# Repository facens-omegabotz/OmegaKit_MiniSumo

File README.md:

# OmegaKit MiniSumo

Repositório dedicado aos projetos de placas de circuito impresso (PCI) desenvolvidas para a categoria Mini Sumô - 500g (Autônomo | RC).

## OmegaKit FX50

Esta pasta diz respeito à versão da placa desenhada para os sensores FX50, da Fox Dynamics. A principal diferença deste desenho para o OmegaKit_RZ60 é a presença de LEDs para a sinalização de recepção de sinal.

[Datasheet FX50](https://github.com/luisf18/FXDevices/blob/main/Sensor_FXS50/Datasheet_FX_S50.pdf)

[Projeto esquemático OmegaKit FX50](./OmegaKit_FX50/OmegaKit_FX50.pdf)

## OmegaKit RZ60

Esta pasta diz respeito à versão da placa desenhada para os sensores RZ60s, da Sumozade. Esta placa liga diretamente os sensores à placa, visto que há LEDs na parte de trás dos sensores para sinalização de detecção.

[Informações RZ60s](https://sumozade.com/rz60s-digital-infrared-sensor--0-60-cm-)

[Projeto esquemático OmegaKit RZ60](./OmegaKit_RZ60/OmegaKit_RZ60.pdf)

## Omegakit Junior

Esta pasta diz respeito à versão da placa dedicada à nova categoria de mini sumô autônomo para juniores. Ela utiliza um Arduino Nano ao invés de um ESP32 DEVKIT V1, e possui 5 entradas analógicas para uso, visto que o Arduino Nano pode converter entradas analógicas em digitais de acordo com a necessidade.

[Projeto esquemático OmegaKit Junior](./OmegaKit_Junior/OmegaKit_Junior.pdf)

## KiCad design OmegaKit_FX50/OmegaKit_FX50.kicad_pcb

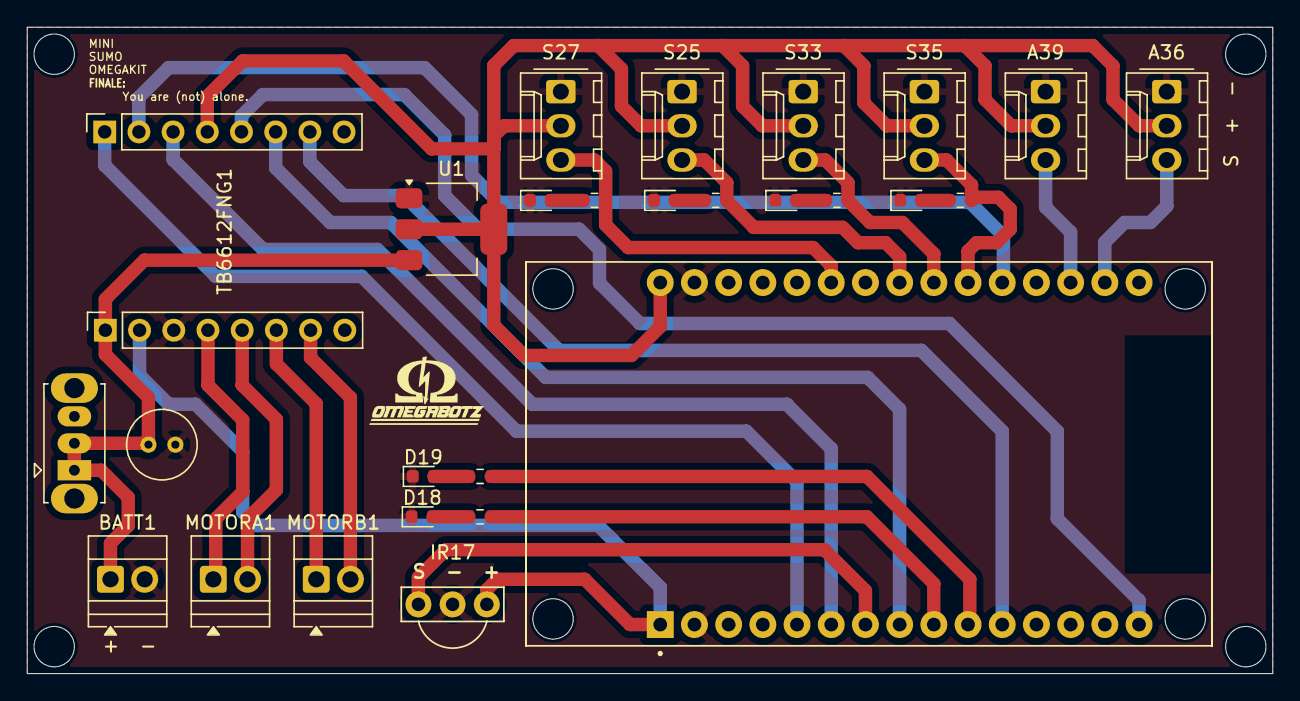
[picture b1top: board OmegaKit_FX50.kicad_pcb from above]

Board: 2 copper layers, 92.5 x 48.0 mm, 27 parts (0 on the bottom side), 29 nets.

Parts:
A36, A39: Conn_01x03_Pin; Molex_KK-254_AE-6410-03A_1x03_P2.54mm_Vertical
BATT1: Borne; TerminalBlock_Xinya_XY308-2.54-2P_1x02_P2.54mm_Horizontal
C1: C_US; C_Radial_D5.0mm_H5.0mm_P2.00mm
D18, D19: LED; LED_0603_1608Metric
DS1, DS2, DS3, DS4: LED; LED_0603_1608Metric
ESP1: ESP32-DEVKIT-V1; MODULE_ESP32_DEVKIT_V1
IR17: TSOP1838
MOTORA1: Borne; TerminalBlock_Xinya_XY308-2.54-2P_1x02_P2.54mm_Horizontal
MOTORB1: Borne; TerminalBlock_Xinya_XY308-2.54-2P_1x02_P2.54mm_Horizontal
R1, R2: 220R; R_0603_1608Metric
RS1, RS2, RS3, RS4: 220R; R_0603_1608Metric
S25, S27, S33, S35: Conn_01x03_Pin; Molex_KK-254_AE-6410-03A_1x03_P2.54mm_Vertical
SW1: SW_CK_OS102011MS2Q; SW_Slide_SPDT_Straight_CK_OS102011MS2Q
TB6612FNG1: Socket_TB6612FNG
U1: AMS1117-5.0; SOT-223-3_TabPin2

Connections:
/A1: A36.3, ESP1.17 (VP)
/A2: A39.3, ESP1.18 (VN)
/AIN1: ESP1.6 (RX2), TB6612FNG1.14 (AIN1)
/AIN2: ESP1.20 (D35), TB6612FNG1.15 (AIN2)
/A_GND: MOTORA1.2, TB6612FNG1.5 (A02)
/A_VCC: MOTORA1.1, TB6612FNG1.4 (A01)
/BATT_VCC: BATT1.1, C1.1, SW1.1 (B), SW1.2 (C), TB6612FNG1.1 (VM), U1.3 (VI)
/BIN1: ESP1.15 (D23), TB6612FNG1.12 (BIN1)
/BIN2: ESP1.8 (D5), TB6612FNG1.11 (BIN2)
/B_GND: MOTORB1.2, TB6612FNG1.7 (B01)
/B_VCC: MOTORB1.1, TB6612FNG1.6 (B02)
/IR_SIGNAL: ESP1.7 (TX2), IR17.1 (OUT)
/LED1: ESP1.10 (D19), R1.2
/LED2: ESP1.9 (D18), R2.2
/PWMA: ESP1.5 (D4), TB6612FNG1.16 (PWMA)
/PWMB: ESP1.11 (D21), TB6612FNG1.10 (PWMB)
/S1: ESP1.21 (D32), RS1.2, S35.3
/S2: ESP1.22 (D33), RS2.2, S33.3
/S3: ESP1.23 (D25), RS3.2, S25.3
/S4: ESP1.25 (D27), RS4.2, S27.3
/VCC: ESP1.1 (3V3), IR17.3 (VCC), TB6612FNG1.2 (VCC)
/V_REG: A36.2, A39.2, ESP1.30 (VIN), S25.2, S27.2, S33.2, S35.2, TB6612FNG1.13 (STBY), U1.2 (VO)
GND: A36.1, A39.1, BATT1.2, C1.2, D18.1 (K), D19.1 (K), DS1.1 (K), DS2.1 (K), DS3.1 (K), DS4.1 (K), ESP1.2 (GND), ESP1.29 (GND), IR17.2 (GND), S25.1, S27.1, S33.1, S35.1, TB6612FNG1.3 (GND), U1.1 (GND)
unnamed: D18.2 (A), R2.1
unnamed: D19.2 (A), R1.1
unnamed: DS1.2 (A), RS1.1
unnamed: DS2.2 (A), RS2.1
unnamed: DS3.2 (A), RS3.1
unnamed: DS4.2 (A), RS4.1

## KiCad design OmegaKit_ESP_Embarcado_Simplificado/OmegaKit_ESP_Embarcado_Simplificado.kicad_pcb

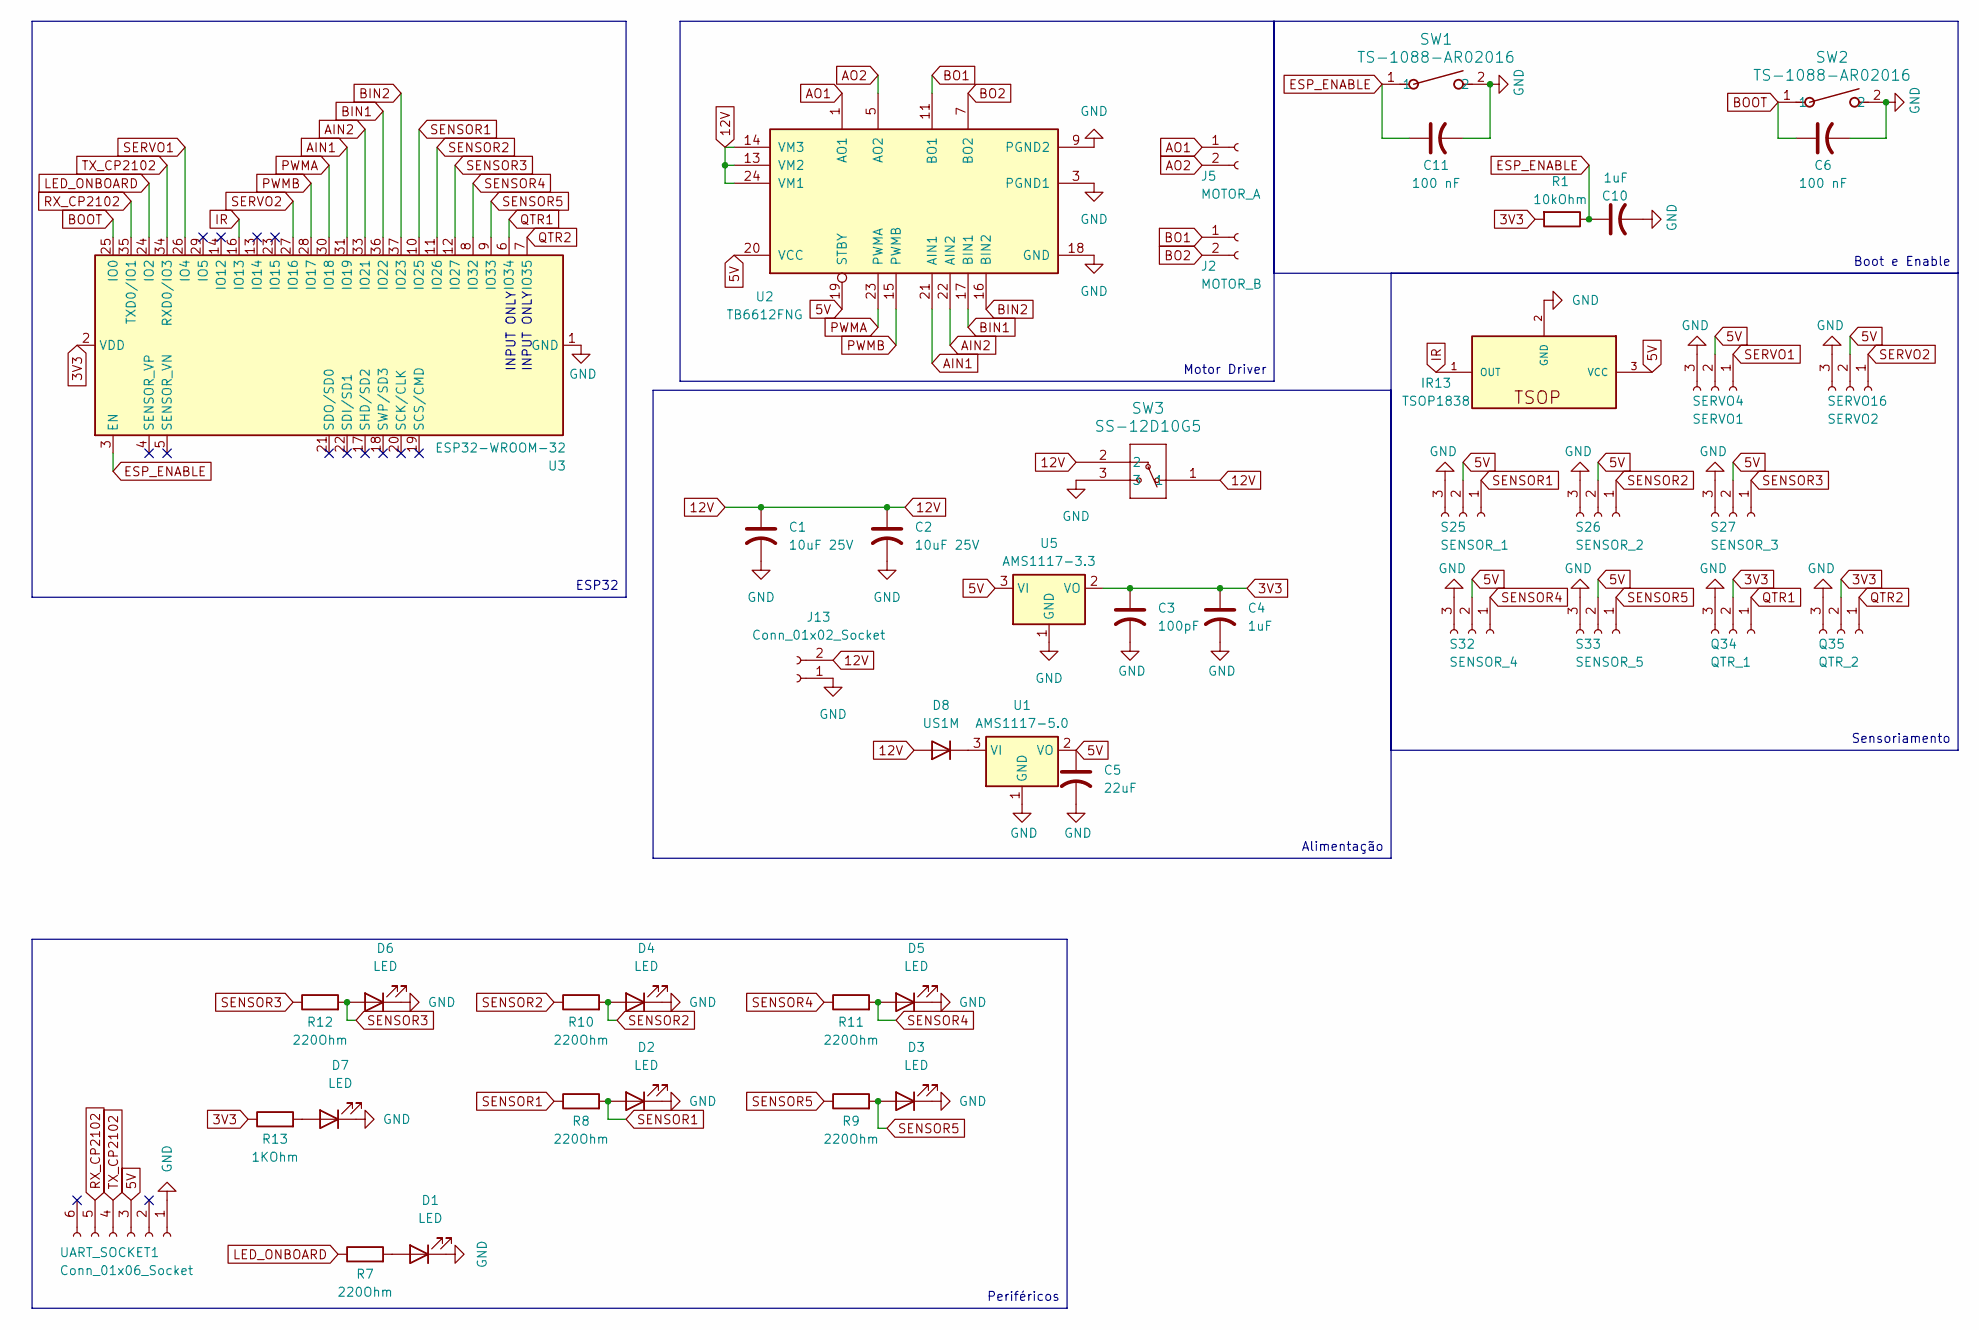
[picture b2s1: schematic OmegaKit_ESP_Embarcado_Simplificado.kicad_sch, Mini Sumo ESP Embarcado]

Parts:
C1, C2: 10uF 25V; C_Elec_4x5.4
C3: 100pF; C_0603_1608Metric_Pad1.08x0.95mm_HandSolder
C4, C10: 1uF; C_0402_1005Metric_Pad0.74x0.62mm_HandSolder
C5: 22uF; C_0603_1608Metric_Pad1.08x0.95mm_HandSolder
C6, C11: 100 nF; C_0201_0603Metric_Pad0.64x0.40mm_HandSolder
D1, D2, D3, D4, D5, D6, D7: LED; LED_0805_2012Metric_Pad1.15x1.40mm_HandSolder
D8: US1M; D_SMA_Handsoldering
IR13: TSOP1838
J2: MOTOR_B; PinHeader_1x02_P2.54mm_Vertical
J5: MOTOR_A; PinHeader_1x02_P2.54mm_Vertical
J13: Conn_01x02_Socket; PinHeader_1x02_P2.54mm_Vertical
Q34: QTR_1; PinHeader_1x03_P2.54mm_Vertical
Q35: QTR_2; PinHeader_1x03_P2.54mm_Vertical
R1: 10kOhm; R_0603_1608Metric_Pad0.98x0.95mm_HandSolder
R7, R8, R9, R10, R11, R12: 220Ohm; R_0805_2012Metric_Pad1.20x1.40mm_HandSolder
R13: 1KOhm; R_0805_2012Metric_Pad1.20x1.40mm_HandSolder
S25: SENSOR_1; PinHeader_1x03_P2.54mm_Vertical
S26: SENSOR_2; PinHeader_1x03_P2.54mm_Vertical
S27: SENSOR_3; PinHeader_1x03_P2.54mm_Vertical
S32: SENSOR_4; PinHeader_1x03_P2.54mm_Vertical
S33: SENSOR_5; PinHeader_1x03_P2.54mm_Vertical
SERVO4: SERVO1; PinHeader_1x03_P2.54mm_Vertical
SERVO16: SERVO2; PinHeader_1x03_P2.54mm_Vertical
SW1, SW2: TS-1088-AR02016; SW_TS-1088_XNP
SW3: SS-12D10G5; SS-12D10G5_XKB
U1: AMS1117-5.0; SOT-223-3_TabPin2
U2: TB6612FNG; SSOP-24_5.3x8.2mm_P0.65mm
U3: ESP32-WROOM-32
U5: AMS1117-3.3; SOT-223-3_TabPin2
UART_SOCKET1: Conn_01x06_Socket; PinHeader_1x06_P2.54mm_Vertical

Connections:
3V3: C3.1, C4.1, Q34.2, Q35.2, R1.2, R13.1, U3.2 (VDD), U5.2 (VO)
5V: C5.1, IR13.3 (VCC), S25.2, S26.2, S27.2, S32.2, S33.2, SERVO4.2, SERVO16.2, U1.2 (VO), U2.19 (STBY), U2.20 (VCC), U5.3 (VI), UART_SOCKET1.3
12V: C1.1, C2.1, D8.2 (A), J13.2, SW3.1, SW3.2, U2.13 (VM2), U2.14 (VM3), U2.24 (VM1)
AIN1: U2.21 (AIN1), U3.31 (IO19)
AIN2: U2.22 (AIN2), U3.33 (IO21)
AO1: J5.1, U2.1 (AO1), U2.2 (AO1)
AO2: J5.2, U2.5 (AO2), U2.6 (AO2)
BIN1: U2.17 (BIN1), U3.36 (IO22)
BIN2: U2.16 (BIN2), U3.37 (IO23)
BO1: J2.1, U2.11 (BO1), U2.12 (BO1)
BO2: J2.2, U2.7 (BO2), U2.8 (BO2)
BOOT: C6.1, SW2.1, U3.25 (IO0)
ESP_ENABLE: C10.1, C11.1, R1.1, SW1.1, U3.3 (EN)
GND: C1.2, C2.2, C3.2, C4.2, C5.2, C6.2, C10.2, C11.2, D1.1 (K), D2.1 (K), D3.1 (K), D4.1 (K), D5.1 (K), D6.1 (K), D7.1 (K), IR13.2 (GND), J13.1, Q34.3, Q35.3, S25.3, S26.3, S27.3, S32.3, S33.3, SERVO4.3, SERVO16.3, SW1.2, SW2.2, SW3.3, U1.1 (GND), U2.3 (PGND1), U2.4 (PGND1), U2.9 (PGND2), U2.10 (PGND2), U2.18 (GND), U3.1 (GND), U3.15 (GND), U3.38 (GND), U3.39 (GND), U5.1 (GND), UART_SOCKET1.1
IR: IR13.1 (OUT), U3.16 (IO13)
LED_ONBOARD: R7.1, U3.24 (IO2)
unnamed: D1.2 (A), R7.2
unnamed: D7.2 (A), R13.2
unnamed: D8.1 (K), U1.3 (VI)
PWMA: U2.23 (PWMA), U3.30 (IO18)
PWMB: U2.15 (PWMB), U3.28 (IO17)
QTR1: Q34.1, U3.6 (IO34)
QTR2: Q35.1, U3.7 (IO35)
RX_CP2102: U3.35 (TXD0/IO1), UART_SOCKET1.5
SENSOR1: D2.2 (A), R8.1, R8.2, S25.1, U3.10 (IO25)
SENSOR2: D4.2 (A), R10.1, R10.2, S26.1, U3.11 (IO26)
SENSOR3: D6.2 (A), R12.1, R12.2, S27.1, U3.12 (IO27)
SENSOR4: D5.2 (A), R11.1, R11.2, S32.1, U3.8 (IO32)
SENSOR5: D3.2 (A), R9.1, R9.2, S33.1, U3.9 (IO33)
SERVO1: SERVO4.1, U3.26 (IO4)
SERVO2: SERVO16.1, U3.27 (IO16)
TX_CP2102: U3.34 (RXD0/IO3), UART_SOCKET1.4

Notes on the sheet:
INPUT ONLY
Motor Driver
Alimentação
Periféricos
Sensoriamento
Boot e Enable
ESP32

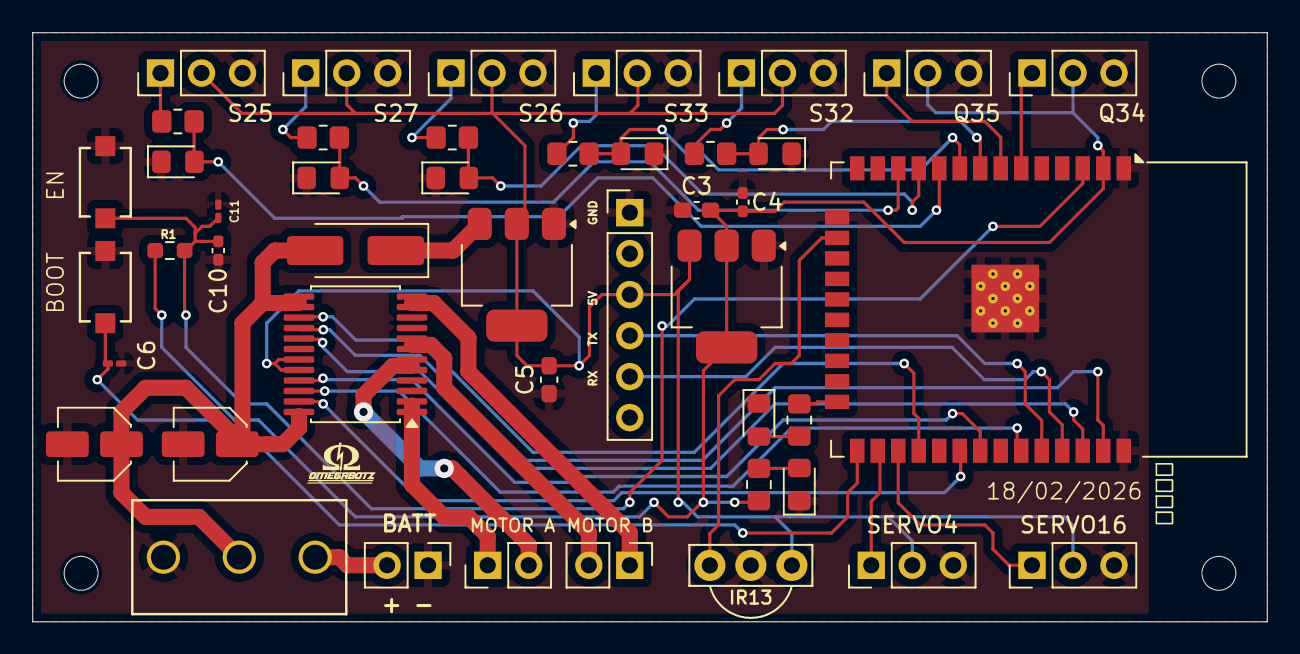
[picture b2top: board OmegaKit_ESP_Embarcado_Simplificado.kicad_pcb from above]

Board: 2 copper layers, 76.5 x 36.5 mm, 45 parts (0 on the bottom side), 32 nets.

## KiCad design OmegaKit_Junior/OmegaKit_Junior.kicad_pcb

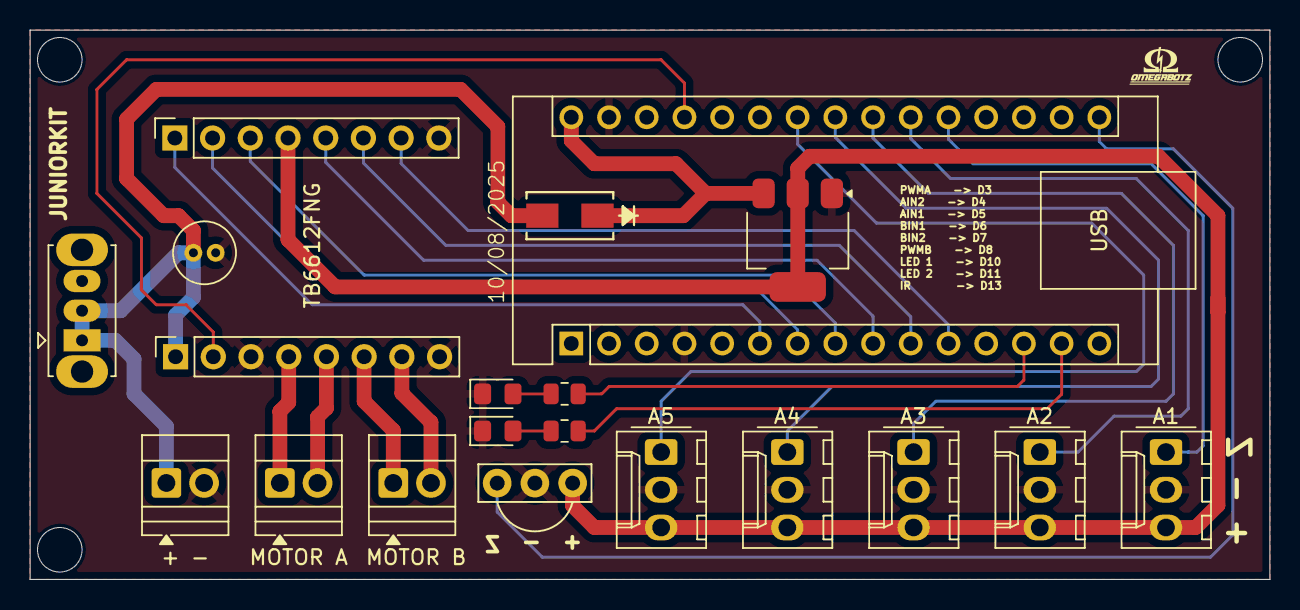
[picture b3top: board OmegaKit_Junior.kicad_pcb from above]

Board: 2 copper layers, 83.5 x 37.0 mm, 19 parts (0 on the bottom side), 24 nets.

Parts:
+ -: Screw_Terminal_01x02; TerminalBlock_Xinya_XY308-2.54-2P_1x02_P2.54mm_Horizontal
A1, A2, A3, A4, A5: Conn_01x03_Pin; Molex_KK-254_AE-6410-03A_1x03_P2.54mm_Vertical
ARDUINO1: Arduino_Nano_v3.x; Arduino_Nano
C1: C_US; C_Radial_D4.0mm_H5.0mm_P1.50mm
D10, D11: LED; LED_0805_2012Metric_Pad1.15x1.40mm_HandSolder
MOTOR A: Screw_Terminal_01x02; TerminalBlock_Xinya_XY308-2.54-2P_1x02_P2.54mm_Horizontal
MOTOR B: Screw_Terminal_01x02; TerminalBlock_Xinya_XY308-2.54-2P_1x02_P2.54mm_Horizontal
R1, R2: 220R; R_0805_2012Metric
REG: AMS1117-5.0; SOT-223-3_TabPin2
RET: US1M-13-F; SMA_DIO
SW1: SW_CK_OS102011MS2Q; SW_Slide_SPDT_Straight_CK_OS102011MS2Q
TB6612FNG: Socket_TB6612FNG
U1: TSOP1838

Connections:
/AIN1: ARDUINO1.8 (D5), TB6612FNG.14 (AIN1)
/AIN2: ARDUINO1.7 (D4), TB6612FNG.15 (AIN2)
/A_GND: MOTOR A.2, TB6612FNG.5 (A02)
/A_VCC: MOTOR A.1, TB6612FNG.4 (A01)
/BATT_VCC: + -.1, ARDUINO1.30 (VIN), C1.1, REG.3 (VI), RET.1, RET.2, SW1.1 (B), SW1.2 (C), TB6612FNG.1 (VM)
/BIN1: ARDUINO1.9 (D6), TB6612FNG.12 (BIN1)
/BIN2: ARDUINO1.10 (D7), TB6612FNG.11 (BIN2)
/B_GND: MOTOR B.2, TB6612FNG.7 (B01)
/B_VCC: MOTOR B.1, TB6612FNG.6 (B02)
/IR_SIGNAL: ARDUINO1.16 (D13), U1.1 (OUT)
/LED1: ARDUINO1.13 (D10), R1.2
/LED2: ARDUINO1.14 (D11), R2.2
/PWMA: ARDUINO1.6 (D3), TB6612FNG.16 (PWMA)
/PWMB: ARDUINO1.11 (D8), TB6612FNG.10 (PWMB)
/S_A1: A1.1, ARDUINO1.20 (A1)
/S_A2: A2.1, ARDUINO1.21 (A2)
/S_A3: A3.1, ARDUINO1.22 (A3)
/S_A4: A4.1, ARDUINO1.23 (A4)
/S_A5: A5.1, ARDUINO1.24 (A5)
/VCC: ARDUINO1.27 (+5V), TB6612FNG.2 (VCC)
/V_REG: A1.3, A2.3, A3.3, A4.3, A5.3, REG.2 (VO), TB6612FNG.13 (STBY), U1.3 (VCC)
GND: + -.2, A1.2, A2.2, A3.2, A4.2, A5.2, ARDUINO1.4 (GND), ARDUINO1.29 (GND), C1.2, D10.1 (K), D11.1 (K), REG.1 (GND), TB6612FNG.3 (GND), TB6612FNG.8 (GND), TB6612FNG.9 (GND), U1.2 (GND)
unnamed: D10.2 (A), R1.1
unnamed: D11.2 (A), R2.1

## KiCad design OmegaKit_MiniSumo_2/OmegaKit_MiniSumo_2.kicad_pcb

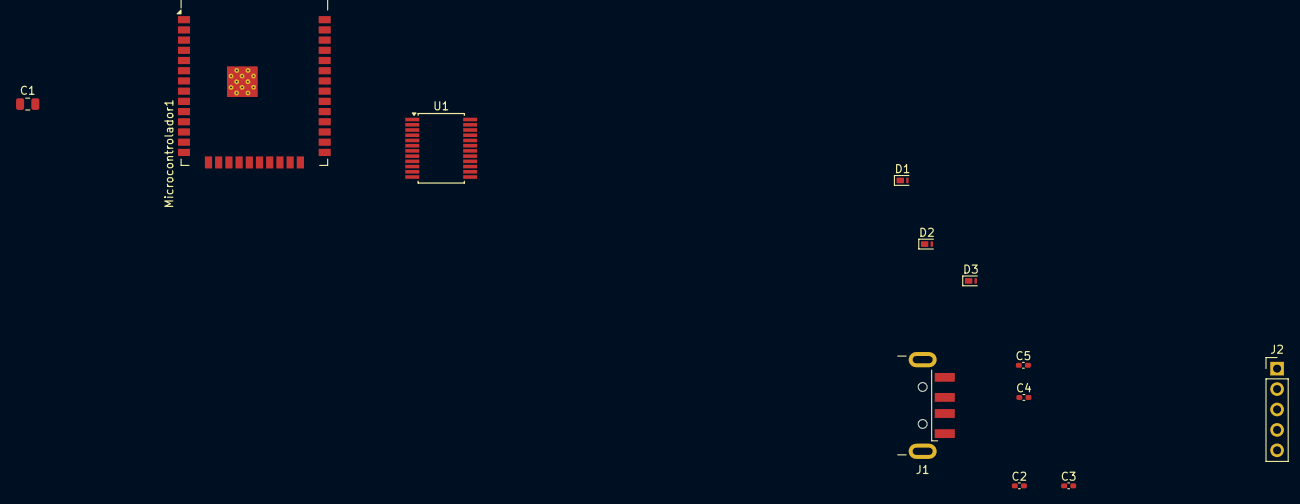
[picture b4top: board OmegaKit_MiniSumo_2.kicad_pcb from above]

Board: 2 copper layers, 12 parts (0 on the bottom side), 12 nets, no tracks yet.

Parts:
C1: C_Small_US; C_0805_2012Metric
C2, C4: 4.7uF; C_0402_1005Metric_Pad0.74x0.62mm_HandSolder
C3, C5: .1uf; C_0402_1005Metric_Pad0.74x0.62mm_HandSolder
D1, D2, D3: PTVS5V0Z1USK; Nexperia_DSN1608-2_1.6x0.8mm
J1: USB_A; USB_A_CNCTech_1001-011-01101_Horizontal
J2: Conn_01x05_Pin; PinHeader_1x05_P2.54mm_Vertical
Microcontrolador1: ESP32-WROOM-32E-R2; ESP32-WROOM-32D
U1: TB6612FNG; SSOP-24_5.3x8.2mm_P0.65mm

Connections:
3V3: C1.1, Microcontrolador1.2 (VDD)
3V3_USB: C4.1, C5.1, J2.1
D+: D3.1 (K), J1.3 (D+)
D-: D2.1 (K), J1.2 (D-)
GND: C1.2, C2.2, C3.2, C4.2, C5.2, D1.2 (A), D2.2 (A), D3.2 (A), J1.4 (GND), J1.5 (Shield), J2.4, Microcontrolador1.1 (GND), Microcontrolador1.15 (GND), Microcontrolador1.38 (GND), Microcontrolador1.39 (GND)
unnamed: U1.1 (AO1), U1.2 (AO1)
unnamed: U1.5 (AO2), U1.6 (AO2)
unnamed: U1.11 (BO1), U1.12 (BO1)
unnamed: U1.7 (BO2), U1.8 (BO2)
unnamed: U1.3 (PGND1), U1.4 (PGND1)
unnamed: U1.9 (PGND2), U1.10 (PGND2)
VBUS: C2.1, C3.1, D1.1 (K), J1.1 (VBUS), J2.5

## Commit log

2025-07-26 Ajustes na pinagem para viabilizar uso do ESP32
2025-07-26 Atualização do PDF + .step
2025-07-26 Atualização PDF esquemático
2025-07-28 Ajustes regulador de tensão + switch e capacitor + não usar pinoGPIO12
2025-07-28 Nova plotagem esquemático
2025-08-04 Correção de pinos + novas plotagens + modelos step + gerbers
2025-08-10 Mudanças RZ60 + Placa juniores
2025-08-10 Registro pinos placa juniores + atualização README.md
2025-08-10 Novo .step placa juniores
2026-02-01 ✨ feat(Omegakit_ESP_Embarcado/*): Inicia novo projeto de eletrônica com ESP-32-WROOM embarcado
2026-02-04 ✨🚧 feat(Omegakit_ESP_Embarcado/*): Inicia desenho da PCB
2026-02-08 ✨🚧 feat(OmegaKit_ESP_Embarcado/*): Monta primeira versão da placa, revisa circuitos, remove CP2102
2026-02-09 ✨ feat(OmegaKit_ESP_Embarcado/*): Adiciona LEDs nos sensores e LED de energia, muda footprint dos capacitores da bateria
2026-02-09 🧹 chore(OmegaKit_ESP_Embarcado/*): Reorganiza projeto, plota projeto em PDF
2026-02-13 ✨ feat: Pequenas revisões no esquemático de OmegaKit_ESP_Embarcado/, criação de OmegaKit_ESP_Embarcado_Simplificado/
2026-04-01 ✨ feat: atualização de todos os arquivps faltantes
